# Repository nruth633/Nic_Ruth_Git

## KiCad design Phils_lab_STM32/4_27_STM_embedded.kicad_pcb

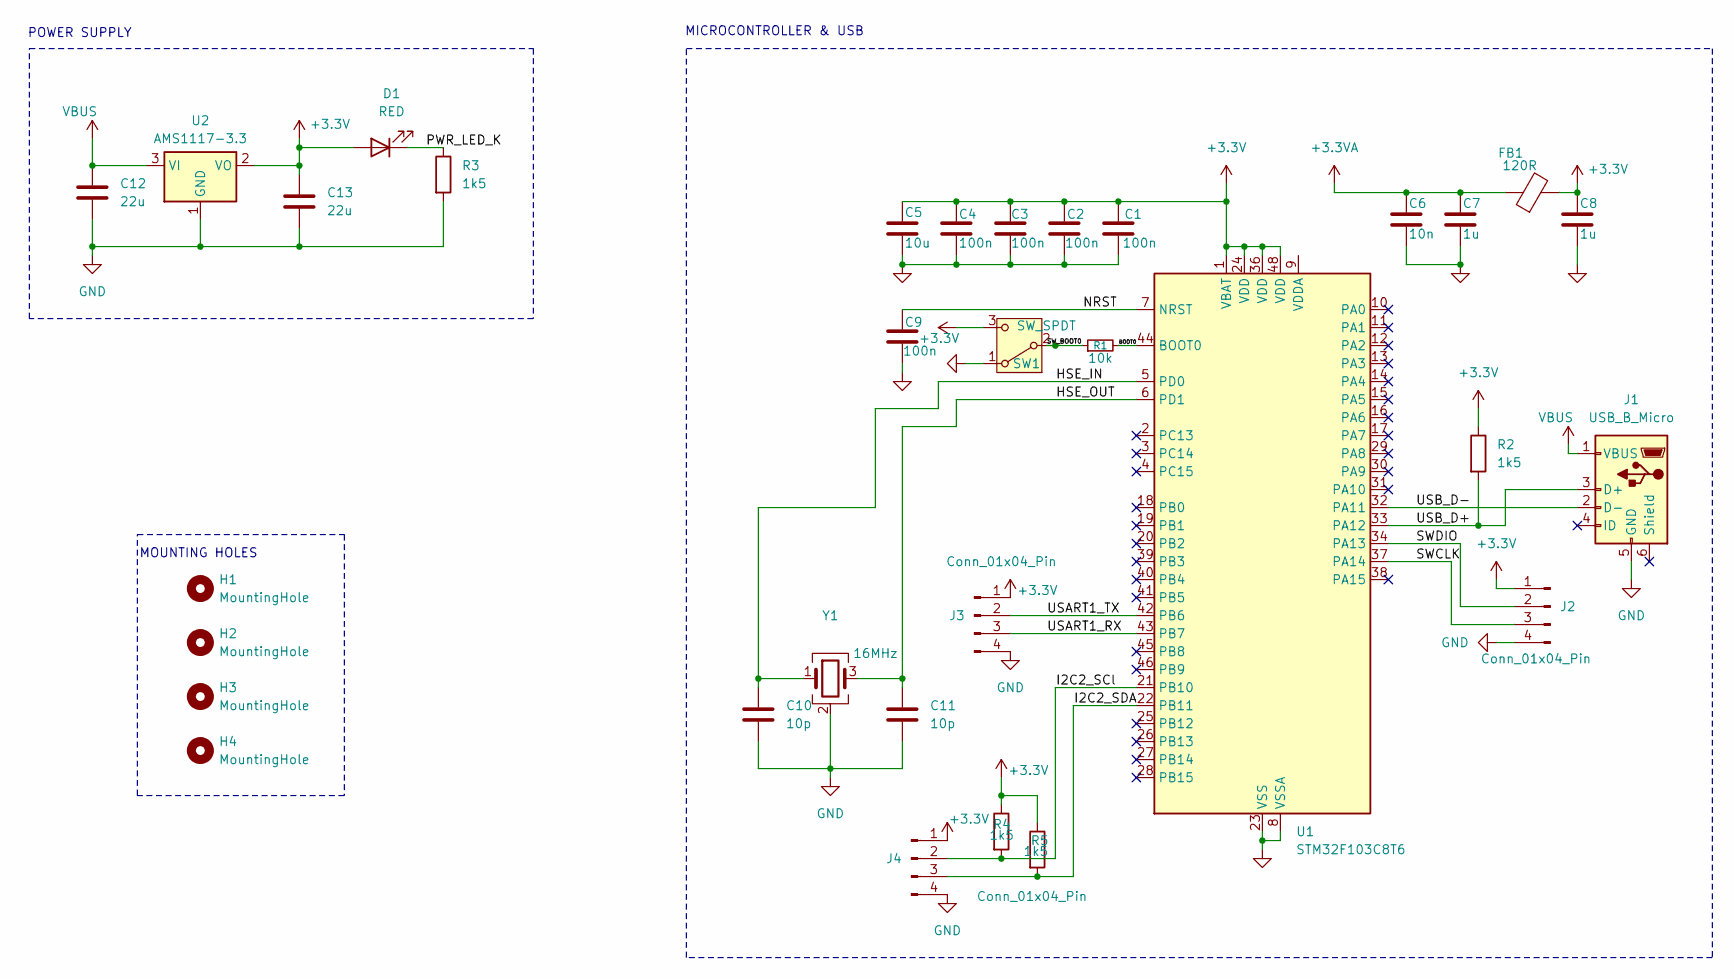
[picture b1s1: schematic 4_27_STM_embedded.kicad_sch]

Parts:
C1, C2, C3, C4, C9: 100n; C_0402_1005Metric
C5: 10u; C_0603_1608Metric
C6: 10n; C_0402_1005Metric
C7, C8: 1u; C_0402_1005Metric
C10, C11: 10p; C_0402_1005Metric
C12, C13: 22u; C_0805_2012Metric
D1: RED; LED_0603_1608Metric
FB1: 120R; L_0603_1608Metric
H1, H2, H3, H4: MountingHole; MountingHole_2.2mm_M2
J1: USB_B_Micro; USB_Micro-B_Wuerth_629105150521
J2, J3, J4: Conn_01x04_Pin; PinHeader_1x04_P2.54mm_Vertical
R1: 10k; R_0402_1005Metric
R2, R3, R4, R5: 1k5; R_0402_1005Metric
SW1: SW_SPDT; SW_SPDT_PCM12
U1: STM32F103C8T6; LQFP-48_7x7mm_P0.5mm
U2: AMS1117-3.3; SOT-223-3_TabPin2
Y1: 16MHz; Crystal_SMD_3225-4Pin_3.2x2.5mm

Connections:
+3.3V: C1.1, C2.1, C3.1, C4.1, C5.1, C8.1, C13.1, D1.2 (A), FB1.2, J2.1, J3.1, J4.1, R2.1, R4.1, R5.1, SW1.3 (C), U1.1 (VBAT), U1.24 (VDD), U1.36 (VDD), U1.48 (VDD), U2.2 (VO)
+3.3VA: C6.1, C7.1, FB1.1
/BOOT0: R1.2, U1.44 (BOOT0)
/HSE_IN: C10.1, U1.5 (PD0), Y1.1
/HSE_OUT: C11.1, U1.6 (PD1), Y1.3
/I2C2_SCl: J4.2, R4.2, U1.21 (PB10)
/I2C2_SDA: J4.3, R5.2, U1.22 (PB11)
/NRST: C9.1, U1.7 (NRST)
/PWR_LED_K: D1.1 (K), R3.1
/SWCLK: J2.3, U1.37 (PA14)
/SWDIO: J2.2, U1.34 (PA13)
/SW_BOOT0: R1.1, SW1.2 (B)
/USART1_RX: J3.3, U1.43 (PB7)
/USART1_TX: J3.2, U1.42 (PB6)
/USB_D+: J1.3 (D+), R2.2, U1.33 (PA12)
/USB_D-: J1.2 (D-), U1.32 (PA11)
GND: C1.2, C2.2, C3.2, C4.2, C5.2, C6.2, C7.2, C8.2, C9.2, C10.2, C11.2, C12.2, C13.2, J1.5 (GND), J2.4, J3.4, J4.4, R3.2, SW1.1 (A), U1.8 (VSSA), U1.23 (VSS), U1.35 (VSS), U1.47 (VSS), U2.1 (GND), Y1.2 (G), Y1.4 (G)
VBUS: C12.1, J1.1 (VBUS), U2.3 (VI)

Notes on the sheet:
MOUNTING HOLES
MICROCONTROLLER & USB
POWER SUPPLY

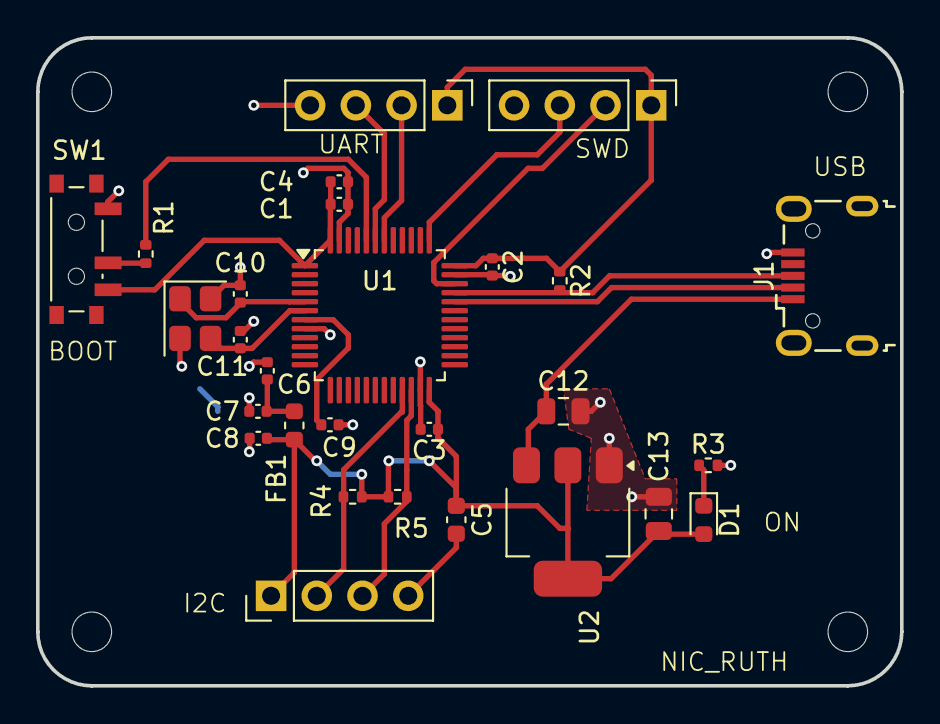
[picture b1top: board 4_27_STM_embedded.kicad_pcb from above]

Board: 2 copper layers, 48.0 x 36.0 mm, 32 parts (0 on the bottom side), 18 nets.

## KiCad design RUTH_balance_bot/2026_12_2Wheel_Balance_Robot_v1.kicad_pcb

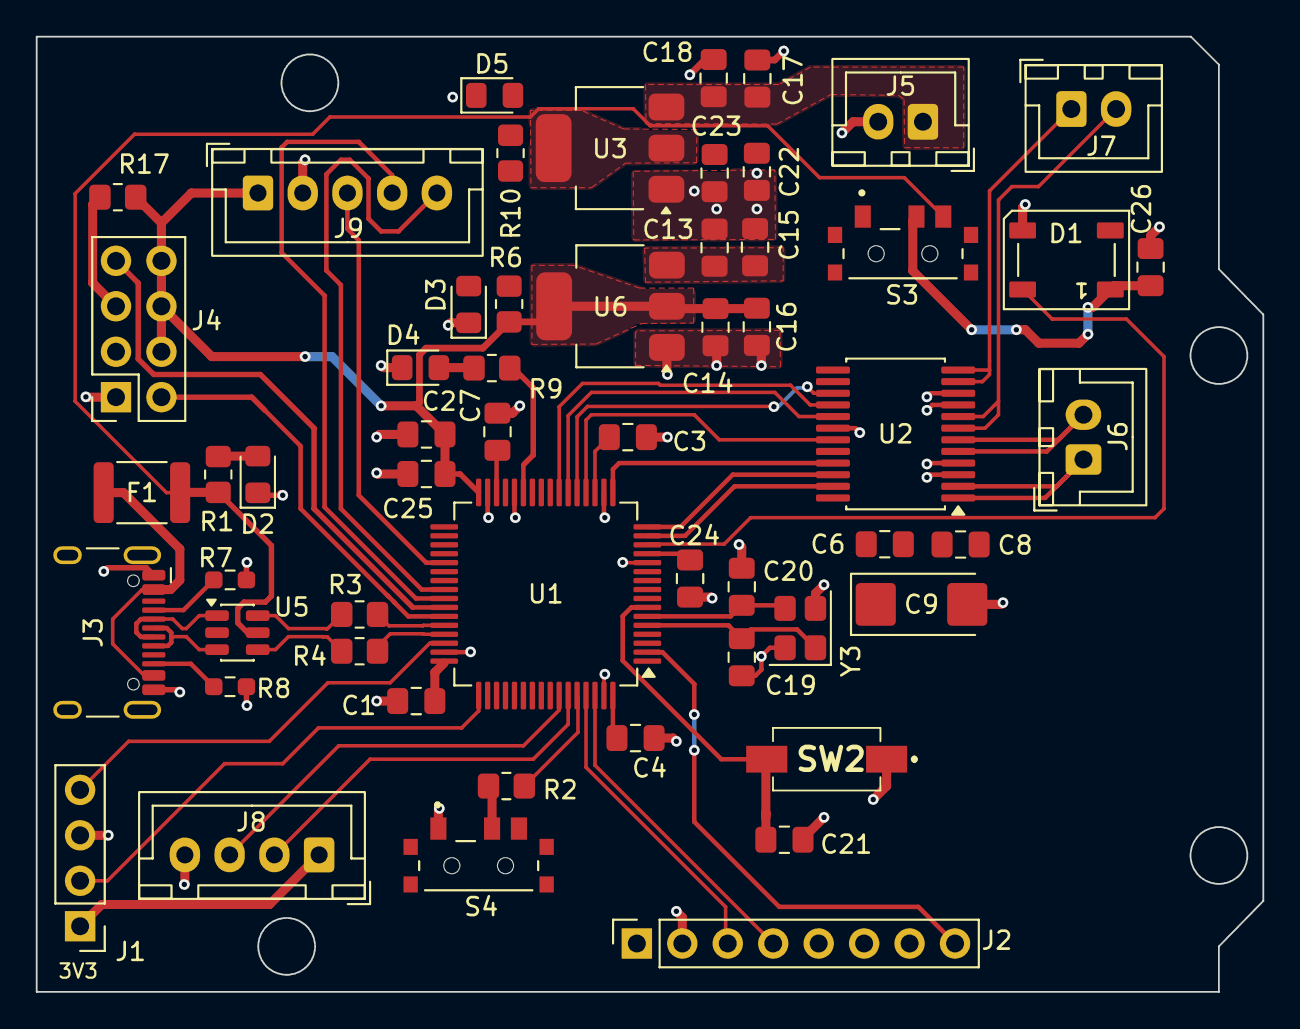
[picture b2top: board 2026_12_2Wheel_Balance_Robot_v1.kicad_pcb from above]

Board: 2 copper layers, 68.6 x 53.4 mm, 56 parts (0 on the bottom side), 51 nets.

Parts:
C1, C2, C3, C4, C6, C8, C13, C14, C17, C22, C24, C26: 0.1uF; C_0805_2012Metric_Pad1.18x1.45mm_HandSolder
C7: 2.2uF; C_0805_2012Metric_Pad1.18x1.45mm_HandSolder
C9: 10uF; CP_EIA-6032-28_Kemet-C_HandSolder
C15, C16, C18, C23, C25: 10uF; C_0805_2012Metric_Pad1.18x1.45mm_HandSolder
C19, C20: 22p; C_0805_2012Metric_Pad1.18x1.45mm_HandSolder
C21: 0.01uF; C_0805_2012Metric_Pad1.18x1.45mm_HandSolder
D1: WS2812B; LED_WS2812B_PLCC4_5.0x5.0mm_P3.2mm
D2: USB_LED; LED_0805_2012Metric_Pad1.15x1.40mm_HandSolder
D3: 3V3_LED; LED_0805_2012Metric_Pad1.15x1.40mm_HandSolder
D4: USER_LED; LED_0805_2012Metric_Pad1.15x1.40mm_HandSolder
D5: 5V_LED; LED_0805_2012Metric_Pad1.15x1.40mm_HandSolder
F1: PTCSMD; Fuse_1812_4532Metric
J1: Conn_01x04; PinHeader_1x04_P2.54mm_Vertical
J2: CONN_MPU6050; PinSocket_1x08_P2.54mm_Vertical
J3: USB_C_Receptacle_USB2.0_14P; USB_C_Receptacle_HCTL_HC-TYPE-C-16P-01A
J4: ESP_Conn; PinSocket_2x04_P2.54mm_Vertical
J5: BATT_CONN; JST_XH_B2B-XH-A_1x02_P2.50mm_Vertical
J6: M1_CONN; JST_XH_B2B-XH-A_1x02_P2.50mm_Vertical
J7: M2_CONN; JST_XH_B2B-XH-A_1x02_P2.50mm_Vertical
J8: ENCODER_CONN; JST_XH_B4B-XH-A_1x04_P2.50mm_Vertical
J9: MT6701_CONN; JST_XH_B5B-XH-A_1x05_P2.50mm_Vertical
R1, R6, R9, R10: 1k; R_0805_2012Metric_Pad1.20x1.40mm_HandSolder
R2, R17: 10k; R_0805_2012Metric_Pad1.20x1.40mm_HandSolder
R3, R4: 22R; R_0805_2012Metric_Pad1.20x1.40mm_HandSolder
R7, R8: 5.1k; R_0603_1608Metric_Pad0.98x0.95mm_HandSolder
S3: REGULATOR_SWITCH; SW_SLW-66527511-SMT-TR
S4: RST_SWITCH; SW_SLW-66527511-SMT-TR
SW2: SW_uP_Reset
U1: STM32F401RBTx; LQFP-64_10x10mm_P0.5mm
U2: TB6612FNG; SSOP-24_5.3x8.2mm_P0.65mm
U3: LD1117S50TR_SOT223; SOT-223-3_TabPin2
U5: USBLC6-2SC6; SOT-23-6
U6: LD1117S33TR_SOT223; SOT-223-3_TabPin2
Y3: 16MHz; Crystal_SMD_Abracon_ABM8G-4Pin_3.2x2.5mm

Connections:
5V_REG: C22.1, C23.1, R10.2, S3.1, U3.2 (VO)
+3.3V: C1.1, C2.1, C3.1, C4.1, C8.1, C14.1, C16.1, C24.1, C25.1, J1.1, J4.4, J4.6, J4.8, J8.1, J9.1, R6.2, R17.1, S4.3, U1.13 (VREF+), U1.19 (VDD), U1.32 (VDD), U1.48 (VDD), U1.64 (VDD), U2.20 (VCC), U6.2 (VO)
+5V: C13.1, C15.1, C26.2, D1.1 (VDD), J2.1, S3.2, U6.3 (VI)
/BOOT0: R2.2, U1.60 (BOOT0)
/CONN_D+: R4.1, U5.4 (I/O2)
/CONN_D-: R3.1, U5.6 (I/O1)
/ENC_A: J8.2, U1.59 (PB7)
/ENC_B: J8.3, U1.58 (PB6)
/ESD_D+: R4.2, U1.45 (USB_OTG_FS_DP)
/ESD_D-: R3.2, U1.44 (USB_OTG_FS_DM)
/ESP_RX: J4.7, U1.42 (USART1_TX)
/ESP_TX: J4.2, U1.43 (USART1_RX)
/IMU_INT: J2.8, U1.2 (PC13)
/IMU_SCL: J2.3, U1.61 (I2C1_SCL)
/IMU_SDA: J2.4, U1.62 (I2C1_SDA)
/MD_AIN1: U1.17 (PA3), U2.21 (AIN1)
/MD_AIN2: U1.16 (PA2), U2.22 (AIN2)
/MD_AO1: J6.1, U2.1 (AO1), U2.2 (AO1)
/MD_AO2: J6.2, U2.5 (AO2), U2.6 (AO2)
/MD_BIN1: U1.22 (PA6), U2.17 (BIN1)
/MD_BIN2: U1.23 (PA7), U2.16 (BIN2)
/MD_BO1: J7.1, U2.11 (BO1), U2.12 (BO1)
/MD_BO2: J7.2, U2.7 (BO2), U2.8 (BO2)
/MD_PWMA: U1.15 (TIM2_CH2), U2.23 (PWMA)
/MD_PWMB: U1.21 (TIM2_CH1), U2.15 (PWMB)
/MD_STBY: U1.20 (PA4), U2.19 (STBY)
/MT_PWM: J9.3, U1.37 (PC6)
/MT_SCL: J9.4, U1.41 (I2C3_SCL)
/MT_SDA: J9.5, U1.40 (I2C3_SDA)
/OSCIN: C19.2, U1.5 (RCC_OSC_IN), Y3.1
/OSCOUT: C20.2, U1.6 (RCC_OSC_OUT), Y3.3
/RESET: C21.1, SW2.2 (B), U1.7 (NRST)
/SWCLK: J1.2, U1.49 (SYS_JTCK-SWCLK)
/SWDIO: J1.4, U1.46 (SYS_JTMS-SWDIO)
/USB_D+: J3.A6 (D+), J3.B6 (D+), U5.3 (I/O2)
/USB_D-: J3.A7 (D-), J3.B7 (D-), U5.1 (I/O1)
/USER_LED: R9.2, U1.27 (PB1)
/WS_DIN: D1.4 (DIN), U1.14 (TIM5_CH1)
GND: C1.2, C2.2, C3.2, C4.2, C6.2, C7.2, C8.2, C9.2, C13.2, C14.2, C15.2, C16.2, C17.2, C18.2, C19.1, C20.1, C21.2, C22.2, C23.2, C24.2, C25.2, C26.1, D1.3 (VSS), D2.1 (K), D3.1 (K), D4.1 (K), D5.1 (K), J1.3, J2.2, J3.A1 (GND), J3.A12 (GND), J3.B1 (GND), J3.B12 (GND), J3.SH (SHIELD), J4.1, J5.2, J8.4, J9.2, R7.1, R8.2, S4.1, SW2.1 (A), U1.12 (VSSA), U1.18 (VSS), U1.28 (PB2), U1.31 (VSS), U1.47 (VSS), U1.63 (VSS), U2.3 (PGND1), U2.4 (PGND1), U2.9 (PGND2), U2.10 (PGND2), U2.18 (GND), U3.1 (GND), U5.2 (GND), U6.1 (GND), Y3.2, Y3.4
unnamed: D2.2 (A), R1.1
unnamed: D3.2 (A), R6.1
unnamed: D4.2 (A), R9.1
unnamed: D5.2 (A), R10.1
unnamed: F1.1, J3.A4 (VBUS), J3.A9 (VBUS), J3.B4 (VBUS), J3.B9 (VBUS)
unnamed: J3.A5 (CC1), R7.2
unnamed: J3.B5 (CC2), R8.1
unnamed: J4.5, R17.2
unnamed: R2.1, S4.2
unnamed: C7.1, U1.30 (VCAP1)
VM: C6.1, C9.1, C17.1, C18.1, J5.1, U2.13 (VM2), U2.14 (VM3), U2.24 (VM1), U3.3 (VI)
Vusb: F1.2, R1.2, S3.3, U5.5 (VBUS)

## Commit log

2026-03-09 DOC C
2026-03-11 MAIN
2026-03-13 Create DOCUMENTATION_D
